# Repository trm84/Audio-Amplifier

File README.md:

# Audio-Amplifier
Audio Amplifier For Electronic Design Class

Univeristy of Akron, Spring of 2018, Electronic Design Audio Amplifier Competition
Designed By Tyler Matthews and Nick Darash

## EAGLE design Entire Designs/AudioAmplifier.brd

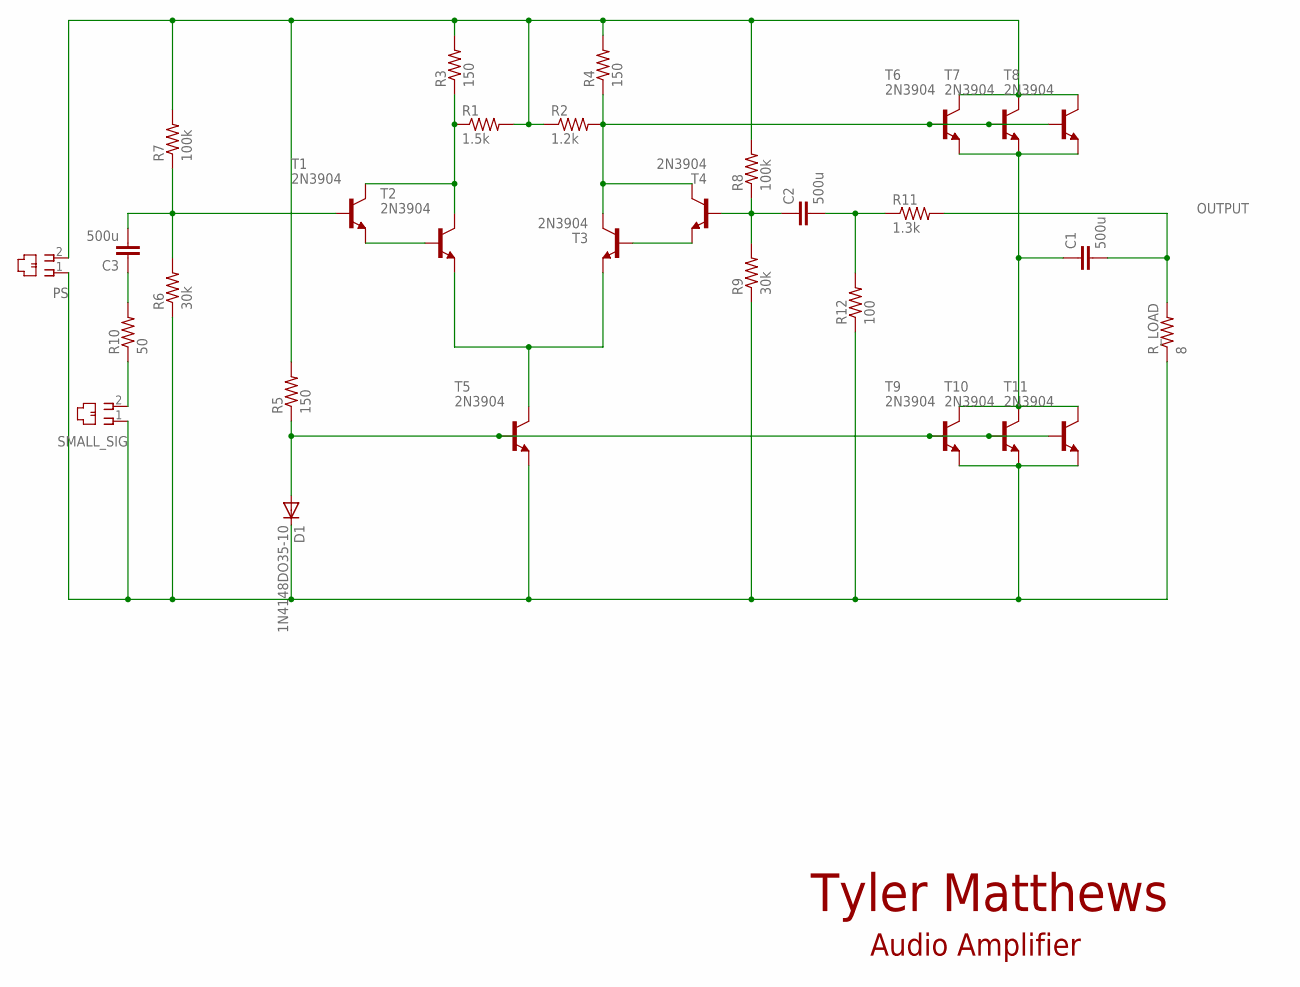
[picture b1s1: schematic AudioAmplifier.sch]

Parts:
C1, C2, C3: 500u; C2.5-2
D1: 1N4148DO35-10; DO35-10
PS: 215876-7
R1: 1.5k; 0204V
R2: 1.2k; 0204V
R3, R4, R5: 150; 0204V
R6, R9: 30k; 0204V
R7, R8: 100k; 0204V
R10: 50; 0204V
R11: 1.3k; 0204V
R12: 100; 0204V
R_LOAD: 8; 0204V
SMALL_SIG: 215876-7
T1, T2, T3, T4, T5, T6, T7, T8, T9, T10, T11: 2N3904; TO92

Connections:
unnamed: T3.2 (B), T4.3 (E)
unnamed: T1.3 (E), T2.2 (B)
unnamed: R1.1, R3.1, T1.1 (C), T2.1 (C)
unnamed: R2.2, R4.1, T3.1 (C), T4.1 (C), T6.2 (B), T7.2 (B), T8.2 (B)
unnamed: T2.3 (E), T3.3 (E), T5.1 (C)
unnamed: D1.A, R5.1, T5.2 (B), T9.2 (B), T10.2 (B), T11.2 (B)
unnamed: C3.2, R6.2, R7.1, T1.2 (B)
unnamed: C1.1, T6.3 (E), T7.3 (E), T8.3 (E), T9.1 (C), T10.1 (C), T11.1 (C)
unnamed: R10.1, SMALL_SIG.2
unnamed: C2.1, R8.1, R9.2, T4.2 (B)
unnamed: C3.1, R10.2
unnamed: PS.2, R1.2, R2.1, R3.2, R4.2, R5.2, R7.2, R8.2, T6.1 (C), T7.1 (C), T8.1 (C)
unnamed: C2.2, R11.1, R12.2
unnamed: D1.C, PS.1, R6.1, R9.1, R12.1, R_LOAD.1, SMALL_SIG.1, T5.3 (E), T9.3 (E), T10.3 (E), T11.3 (E)
OUTPUT: C1.2, R11.2, R_LOAD.2

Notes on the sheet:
Audio Amplifier
Tyler Matthews

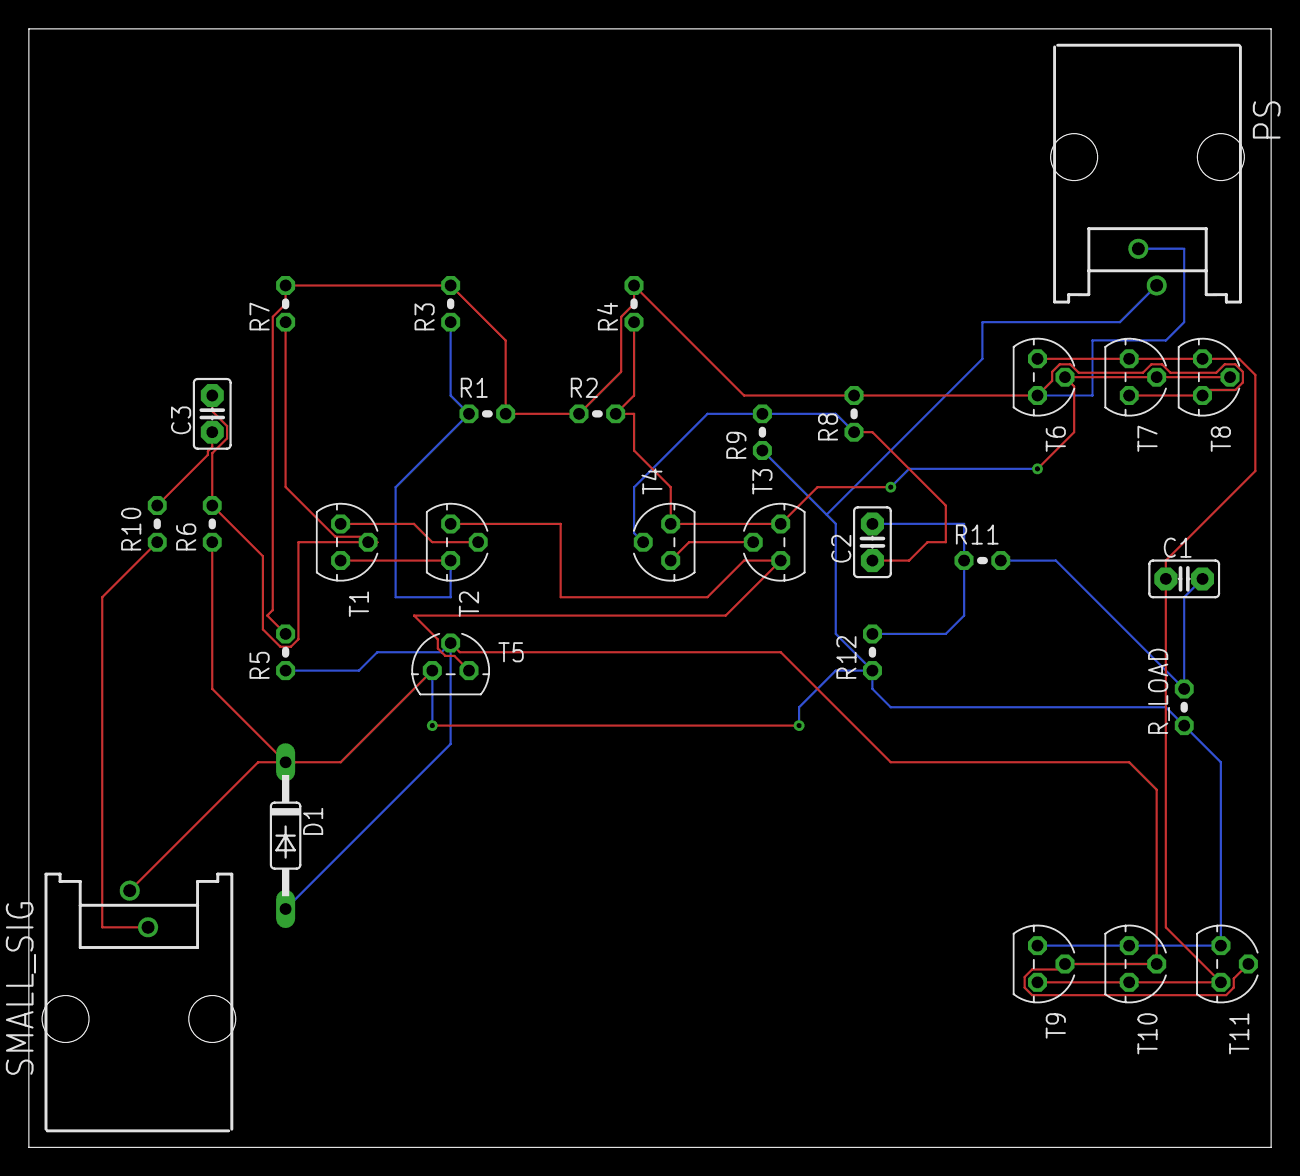
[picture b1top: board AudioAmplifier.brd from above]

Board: 2 copper layers, 86.0 x 77.5 mm, 30 parts (0 on the bottom side), 15 nets.

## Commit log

2018-04-17 udpate
2018-04-21 Added the Differential Pair With Active Loading.
2018-04-21 Updated Diff Pair With Active Load Amplifier
